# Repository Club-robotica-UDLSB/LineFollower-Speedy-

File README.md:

# LineFollower-Speedy-
Documentación del desarrollo del Seguidor de línea (El speedy)  

```plaintext
line_follower_project/
├── docs/                        # Documentación del proyecto
│   ├── README.md                # Descripción del proyecto
│   ├── schematics/              # Diagramas eléctricos y electrónicos
│   │   ├── circuit_diagram.png
│   │   └── PCB_design.pdf
│   └── requirements.md          # Lista de requisitos de hardware y software
├── hardware/                    # Archivos relacionados con el hardware
│   ├── BOM.csv                  # Lista de materiales (Bill of Materials)
│   ├── chassis_design/          # Diseños mecánicos (CAD)
│   │   ├── chassis.stl
│   │   └── chassis.fusion360
│   ├── sensors/                 # Información sobre sensores
│   │   └── sensor_datasheets/
│   │       └── IR_sensor.pdf
│   ├── motor_drivers/           # Archivos de controladores de motores
│   │   └── motor_driver_schematic.png
│   └── microcontroller/         # Configuración del microcontrolador
│       ├── pinout_diagram.png
│       └── firmware.hex
├── software/                    # Código fuente y programas
│   ├── main/                    # Código principal
│   │   ├── main.c
│   │   └── main.h
│   ├── libraries/               # Librerías reutilizables
│   │   ├── PID_controller.c
│   │   └── motor_control.c
│   ├── test/                    # Código para pruebas
│   │   ├── test_pid_controller.c
│   │   └── test_sensors.c
│   └── README.md                # Guía para compilar e instalar
├── tests/                       # Pruebas físicas y simulaciones
│   ├── simulations/             # Simulaciones virtuales
│   │   └── line_follower_simulation.py
│   ├── performance_logs/        # Registros de pruebas de rendimiento
│   │   ├── test_1_results.log
│   │   └── test_2_results.log
│   └── README.md                # Guía de pruebas
├── media/                       # Fotos, videos y otros recursos multimedia
│   ├── videos/
│   │   └── demo_video.mp4
│   └── images/
│       ├── prototype.jpg
│       └── testing.jpg
├── LICENSE                      # Licencia del proyecto
├── README.md                    # Introducción y explicación del proyecto
├── .gitignore                   # Archivos y carpetas a ignorar por Git
└── Makefile                     # Configuración para compilar el proyecto
```

## Descripción de las Carpetas y Archivos

### `docs/`
- **`README.md`**: Descripción general del proyecto.
- **`schematics/`**: Contiene diagramas eléctricos y diseños de PCB.
- **`requirements.md`**: Detalla los requisitos de hardware y software.

### `hardware/`
- **`BOM.csv`**: Lista de materiales necesarios para el proyecto.
- **`chassis_design/`**: Archivos de diseño mecánico del chasis.
- **`sensors/`**: Información técnica sobre los sensores utilizados.
- **`motor_drivers/`**: Esquemáticos de controladores de motores.
- **`microcontroller/`**: Configuración y firmware del microcontrolador.

### `software/`
- **`main/`**: Código principal del proyecto.
- **`libraries/`**: Librerías reutilizables (como controladores PID o control de motores).
- **`test/`**: Scripts para probar diferentes partes del sistema.

### `tests/`
- **`simulations/`**: Contiene simulaciones virtuales del robot.
- **`performance_logs/`**: Registros de pruebas realizadas en el hardware.

### `media/`
- **`videos/`**: Videos de demostración o pruebas del robot.
- **`images/`**: Fotos del prototipo, resultados de pruebas, etc.

### Archivos Raíz
- **`LICENSE`**: Licencia del proyecto.
- **`README.md`**: Introducción al proyecto.
- **`.gitignore`**: Archivos o carpetas que Git debe ignorar.
- **`Makefile`**: Instrucciones para compilar y ejecutar el proyecto.

---

## Notas Adicionales

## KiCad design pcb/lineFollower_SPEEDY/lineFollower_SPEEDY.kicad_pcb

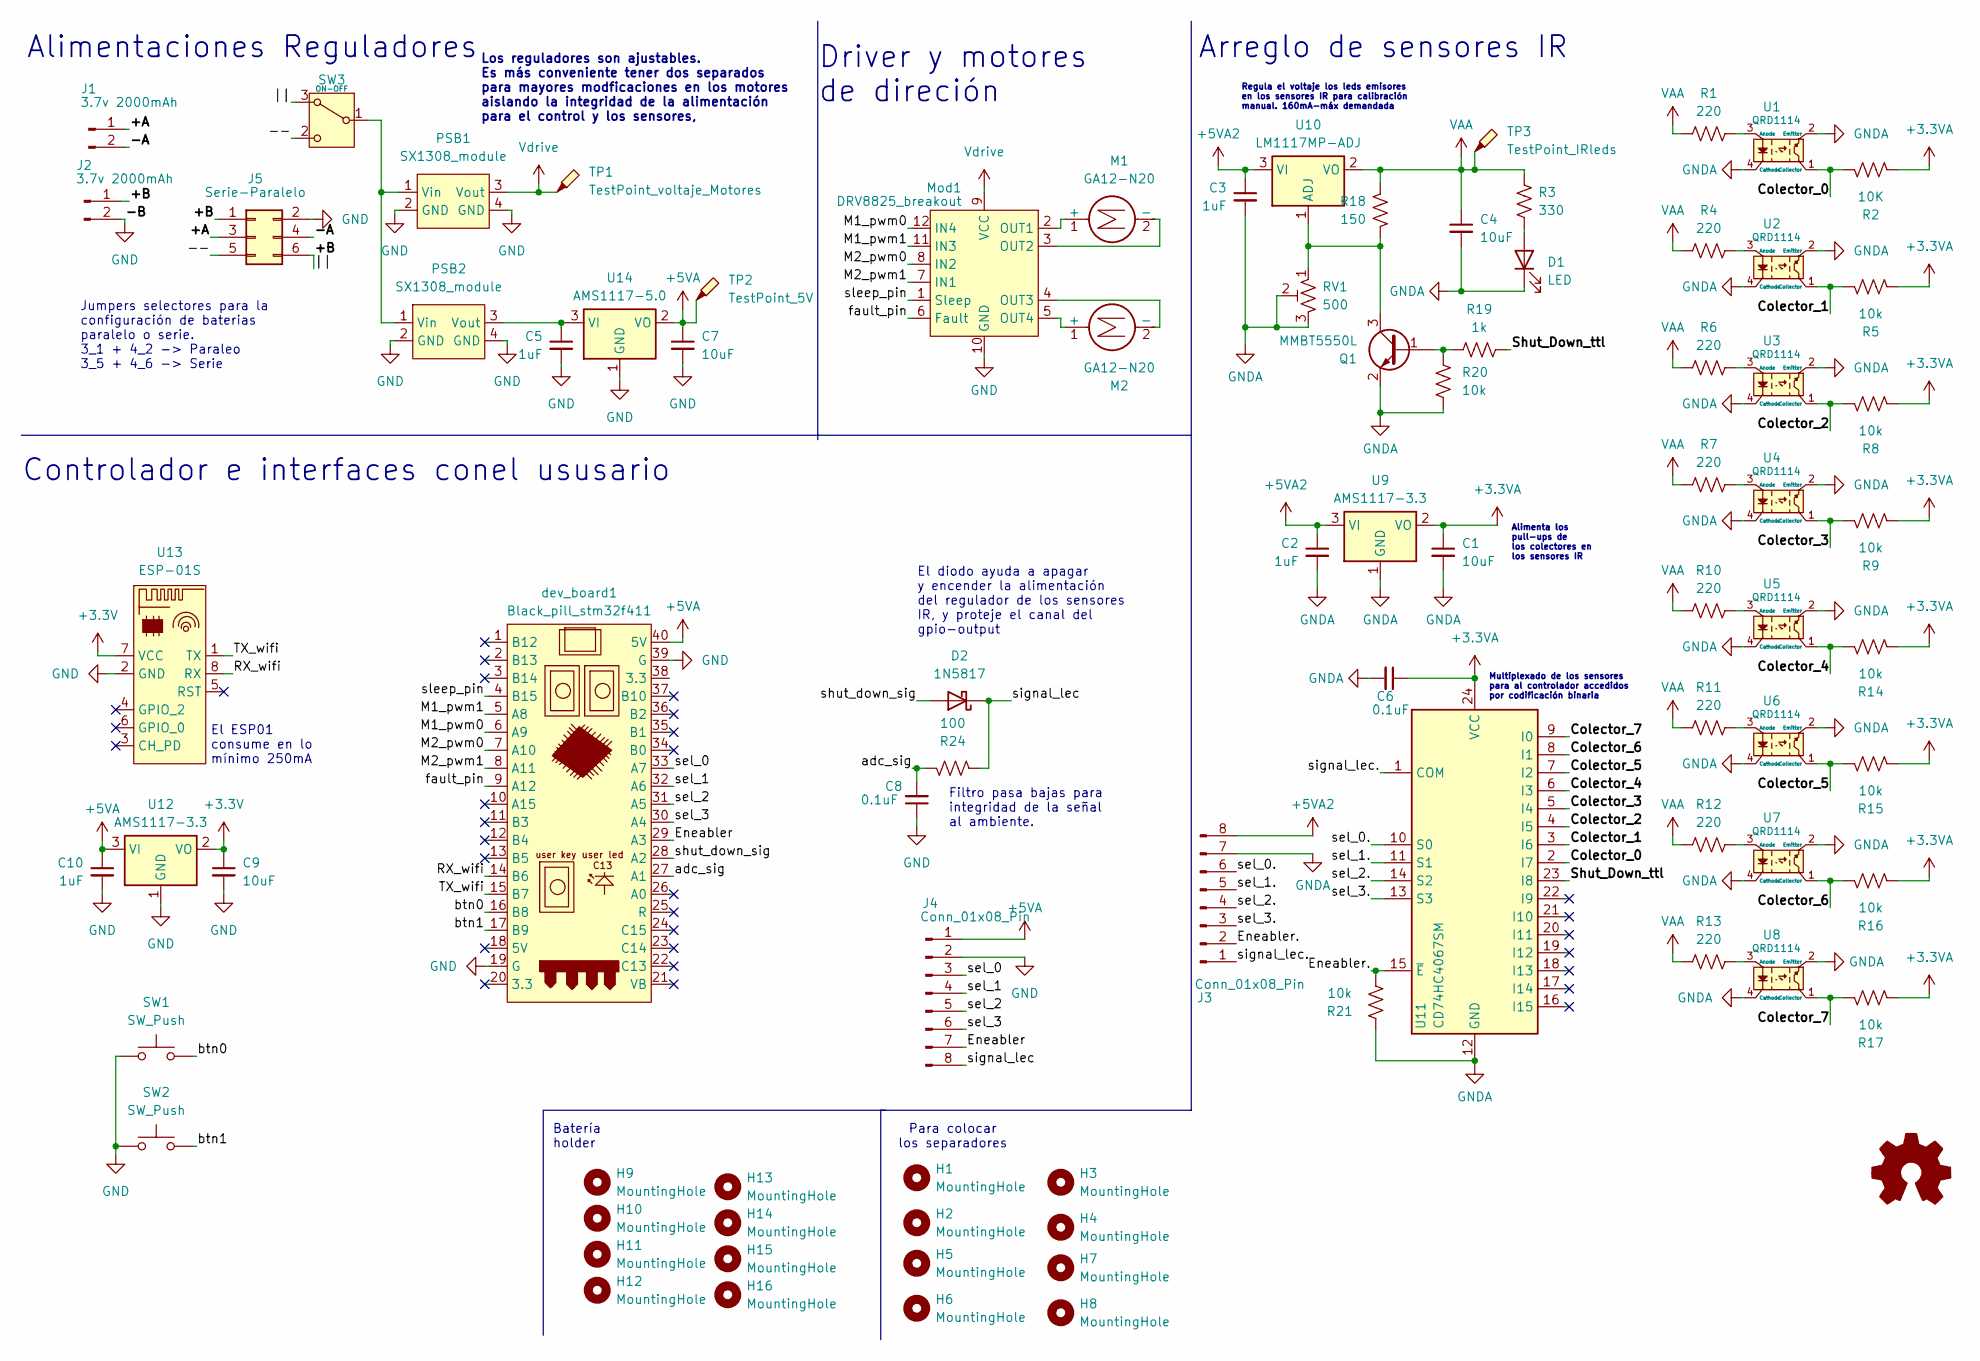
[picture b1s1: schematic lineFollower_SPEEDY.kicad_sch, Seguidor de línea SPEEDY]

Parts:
C1, C4, C7, C9: 10uF; C_0603_1608Metric_Pad1.08x0.95mm_HandSolder
C2, C3, C5, C10: 1uF; C_0603_1608Metric_Pad1.08x0.95mm_HandSolder
C6, C8: 0.1uF; C_0603_1608Metric_Pad1.08x0.95mm_HandSolder
D1: LED; LED_1206_3216Metric_Pad1.42x1.75mm_HandSolder
D2: 1N5817; D_DO-41_SOD81_P10.16mm_Horizontal
H1, H2, H3, H4, H5, H6, H7, H8, H9, H10, H11, H12, H13, H14, H15, H16: MountingHole; MountingHole_2.2mm_M2
J1, J2: 3.7v 2000mAh; JST_PH_S2B-PH-K_1x02_P2.00mm_Horizontal
J3, J4: Conn_01x08_Pin; PinHeader_1x08_P2.54mm_Horizontal
J5: Serie-Paralelo; PinHeader_2x03_P2.54mm_Vertical
M1, M2: GA12-N20; motor
Mod1: DRV8825_breakout; DRV8833_mod
PSB1, PSB2: SX1308_module; SX1308_mod
Q1: MMBT5550L; SOT-23
R1, R4, R6, R7, R10, R11, R12, R13: 220; R_0805_2012Metric_Pad1.20x1.40mm_HandSolder
R2: 10K; R_0805_2012Metric_Pad1.20x1.40mm_HandSolder
R3: 330; R_0805_2012Metric_Pad1.20x1.40mm_HandSolder
R5, R8, R9, R14, R15, R16, R17, R20, R21: 10k; R_0805_2012Metric_Pad1.20x1.40mm_HandSolder
R18: 150; R_0805_2012Metric_Pad1.20x1.40mm_HandSolder
R19: 1k; R_0805_2012Metric_Pad1.20x1.40mm_HandSolder
R24: 100; R_0805_2012Metric_Pad1.20x1.40mm_HandSolder
RV1: 500; Potentiometer_Bourns_3296W_Vertical
SW1, SW2: SW_Push; SW_Tactile_SPST_NO_Straight_CK_PTS636Sx25SMTRLFS
SW3: ON-OFF; SW_Slide-03_Wuerth-WS-SLTV_10x2.5x6.4_P2.54mm
TP1: TestPoint_voltaje_Motores; TestPoint_Loop_D2.54mm_Drill1.5mm_Beaded
TP2: TestPoint_5V; TestPoint_Loop_D2.54mm_Drill1.5mm_Beaded
TP3: TestPoint_IRleds; TestPoint_Loop_D2.54mm_Drill1.5mm_Beaded
U1, U2, U3, U4, U5, U6, U7, U8: QRD1114
U9, U12: AMS1117-3.3; SOT-223-3_TabPin2
U10: LM1117MP-ADJ; SOT-223-3_TabPin2
U11: CD74HC4067SM; SSOP-24_5.3x8.2mm_P0.65mm
U13: ESP-01S; ESP-01
U14: AMS1117-5.0; SOT-223-3_TabPin2
dev_board1: Black_pill_stm32f411; Electrosmith_Daisy_Seed

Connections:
+3.3V: C9.1, U12.2 (VO), U13.7 (VCC)
+3.3VA: C1.1, C6.1, R2.2, R5.2, R8.2, R9.2, R14.2, R15.2, R16.2, R17.2, U9.2 (VO), U11.24 (VCC)
+5VA: C7.1, C10.1, J4.1, TP2.1, U12.3 (VI), U14.2 (VO), dev_board1.40 (5V)
+5VA2: C2.1, C3.1, J3.8, U9.3 (VI), U10.3 (VI)
/+A: J1.1, J5.3
/+B: J2.1, J5.1, J5.6, SW3.3 (A)
/--: J5.5, SW3.2 (C)
/-A: J1.2, J5.4
/Colector_0: R2.1, U1.1 (Collector), U11.2 (I7)
/Colector_1: R5.1, U2.1 (Collector), U11.3 (I6)
/Colector_2: R8.1, U3.1 (Collector), U11.4 (I5)
/Colector_3: R9.1, U4.1 (Collector), U11.5 (I4)
/Colector_4: R14.1, U5.1 (Collector), U11.6 (I3)
/Colector_5: R15.1, U6.1 (Collector), U11.7 (I2)
/Colector_6: R16.1, U7.1 (Collector), U11.8 (I1)
/Colector_7: R17.1, U8.1 (Collector), U11.9 (I0)
/Eneabler: J4.7, dev_board1.29 (A3)
/Eneabler.: J3.2, R21.2, U11.15 (~E)
/M1_pwm0: Mod1.12 (IN4), dev_board1.6 (A9)
/M1_pwm1: Mod1.11 (IN3), dev_board1.5 (A8)
/M2_pwm0: Mod1.8 (IN2), dev_board1.7 (A10)
/M2_pwm1: Mod1.7 (IN1), dev_board1.8 (A11)
/RX_wifi: U13.8 (RX), dev_board1.14 (B6)
/Shut_Down_ttl: R19.1, U11.23 (I8)
/TX_wifi: U13.1 (TX), dev_board1.15 (B7)
/adc_sig: C8.2, R24.2, dev_board1.27 (A1)
/btn0: SW1.2, dev_board1.16 (B8)
/btn1: SW2.2, dev_board1.17 (B9)
/fault_pin: Mod1.6 (Fault), dev_board1.9 (A12)
/sel_0: J4.3, dev_board1.33 (A7)
/sel_0.: J3.6, U11.10 (S0)
/sel_1: J4.4, dev_board1.32 (A6)
/sel_1.: J3.5, U11.11 (S1)
/sel_2: J4.5, dev_board1.31 (A5)
/sel_2.: J3.4, U11.14 (S2)
/sel_3: J4.6, dev_board1.30 (A4)
/sel_3.: J3.3, U11.13 (S3)
/shut_down_sig: D2.2 (A), dev_board1.28 (A2)
/signal_lec: D2.1 (K), J4.8, R24.1
/signal_lec.: J3.1, U11.1 (COM)
/sleep_pin: Mod1.1 (Sleep), dev_board1.4 (B15)
GND: C5.2, C7.2, C8.1, C9.2, C10.2, J2.2, J4.2, J5.2, Mod1.10 (GND), PSB1.2 (GND), PSB1.4 (GND), PSB2.2 (GND), PSB2.4 (GND), SW1.1, SW2.1, U12.1 (GND), U13.2 (GND), U14.1 (GND), dev_board1.19 (G), dev_board1.39 (G)
GNDA: C1.2, C2.2, C3.2, C4.2, C6.2, D1.1 (K), J3.7, Q1.2 (E), R20.2, R21.1, RV1.2, RV1.3, U1.2 (Emitter), U1.4 (Cathode), U2.2 (Emitter), U2.4 (Cathode), U3.2 (Emitter), U3.4 (Cathode), U4.2 (Emitter), U4.4 (Cathode), U5.2 (Emitter), U5.4 (Cathode), U6.2 (Emitter), U6.4 (Cathode), U7.2 (Emitter), U7.4 (Cathode), U8.2 (Emitter), U8.4 (Cathode), U9.1 (GND), U11.12 (GND)
unnamed: D1.2 (A), R3.1
unnamed: M1.1 (+), Mod1.2 (OUT1)
unnamed: M1.2 (-), Mod1.3 (OUT2)
unnamed: M2.1 (+), Mod1.5 (OUT4)
unnamed: M2.2 (-), Mod1.4 (OUT3)
unnamed: PSB1.1 (Vin), PSB2.1 (Vin), SW3.1 (B)
unnamed: C5.1, PSB2.3 (Vout), U14.3 (VI)
unnamed: Q1.1 (B), R19.2, R20.1
unnamed: Q1.3 (C), R18.1, RV1.1, U10.1 (ADJ)
unnamed: R1.2, U1.3 (Anode)
unnamed: R4.2, U2.3 (Anode)
unnamed: R6.2, U3.3 (Anode)
unnamed: R7.2, U4.3 (Anode)
unnamed: R10.2, U5.3 (Anode)
unnamed: R11.2, U6.3 (Anode)
unnamed: R12.2, U7.3 (Anode)
unnamed: R13.2, U8.3 (Anode)
VAA: C4.1, R1.1, R3.2, R4.1, R6.1, R7.1, R10.1, R11.1, R12.1, R13.1, R18.2, TP3.1, U10.2 (VO)
Vdrive: Mod1.9 (VCC), PSB1.3 (Vout), TP1.1

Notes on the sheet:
Driver y motores de direción
Multiplexado de los sensores para al controlador accedidos por codificación binaria
El ESP01 consume en lo mínimo 250mA
El diodo ayuda a apagar y encender la alimentación del regulador de los sensores IR, y proteje el canal del gpio-output
Alimenta los pull-ups de los colectores en los sensores IR
Arreglo de sensores IR
Los reguladores son ajustables. Es más conveniente tener dos separados para mayores modficaciones en los motores aislando la integridad de la alimentación para el control y los sensores,
Regula el voltaje los leds emisores en los sensores IR para calibración manual. 160mA-máx demandada
Batería holder
Jumpers selectores para la configuración de baterias paralelo o serie. 3_1 + 4_2 -> Paraleo 3_5 + 4_6 -> Serie
Filtro pasa bajas para integridad de la señal al ambiente.
Alimentaciones Reguladores
Controlador e interfaces conel ususario
Para colocar los separadores

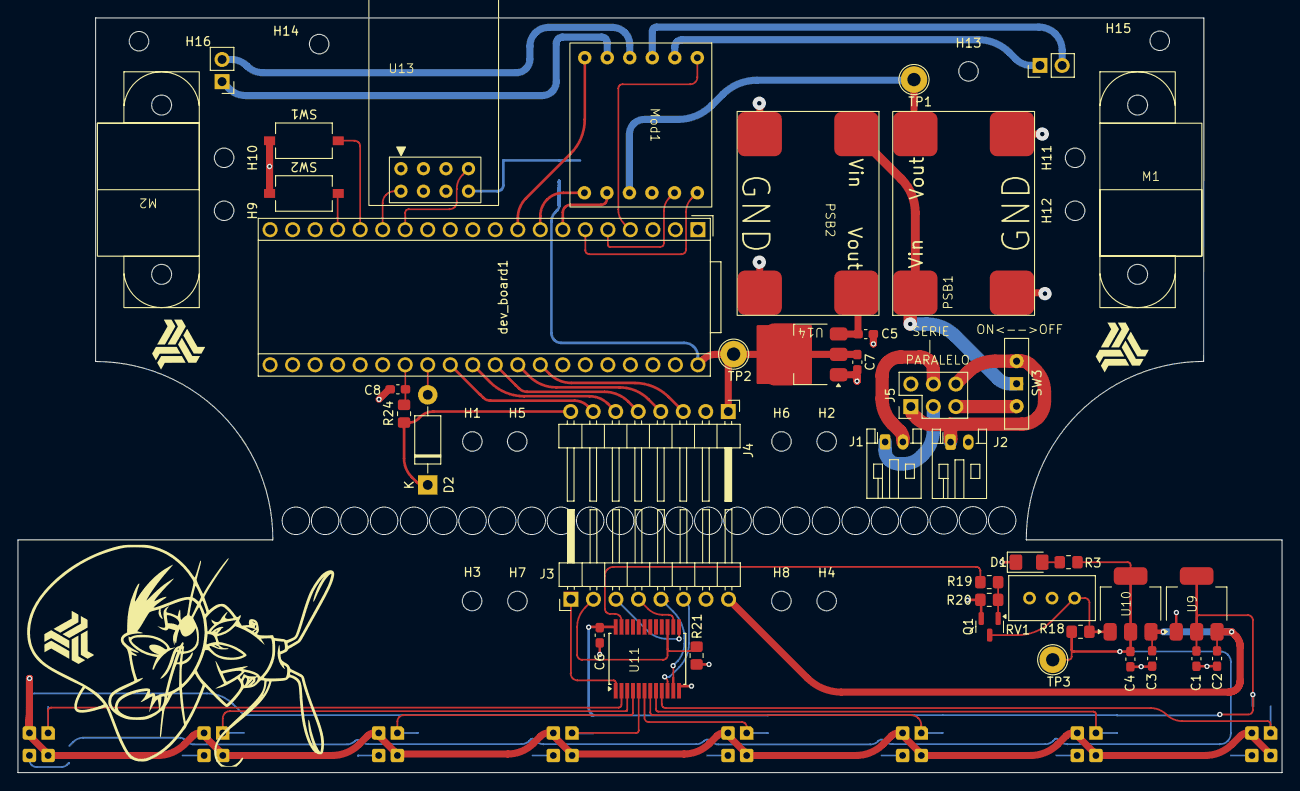
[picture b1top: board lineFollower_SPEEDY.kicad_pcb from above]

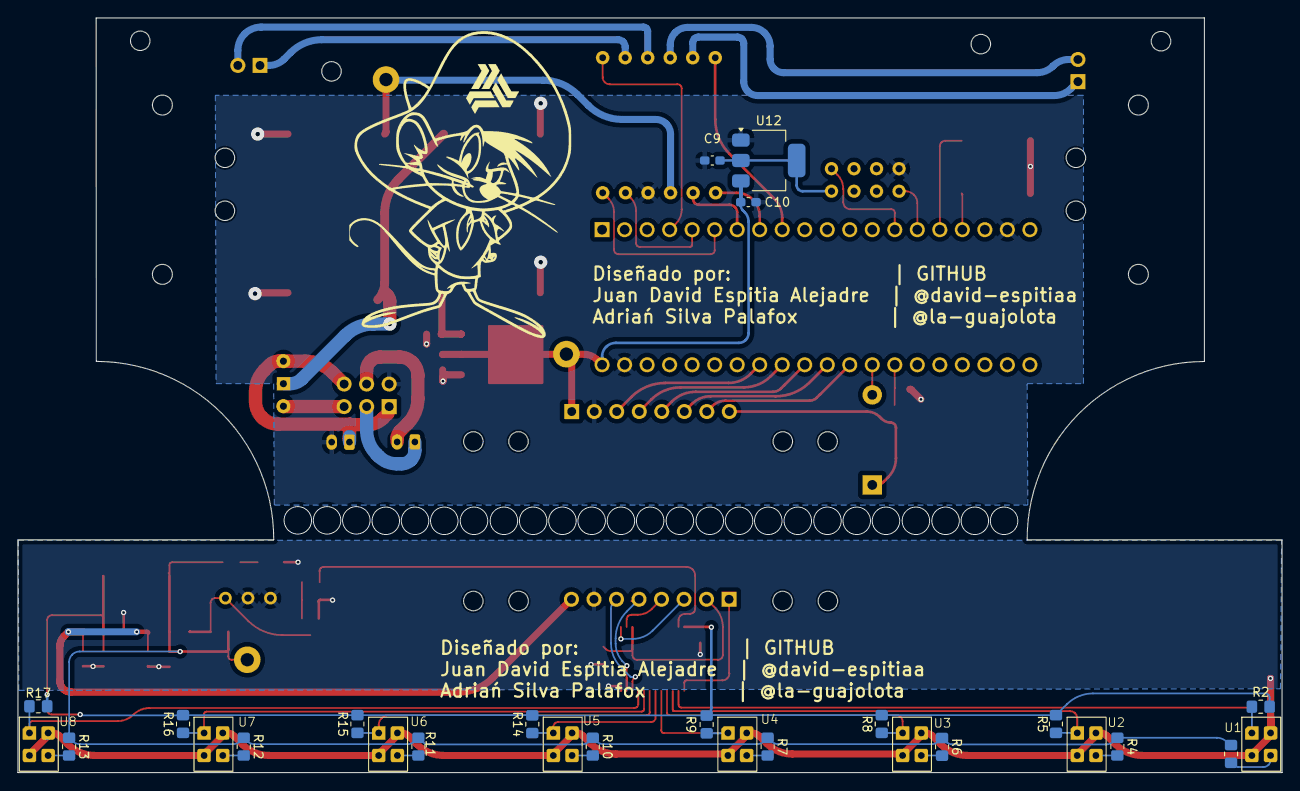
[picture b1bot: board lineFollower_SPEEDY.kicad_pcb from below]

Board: 2 copper layers, 142.6 x 85.1 mm, 83 parts (27 on the bottom side), 62 nets.

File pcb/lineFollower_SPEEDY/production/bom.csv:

Designator,Footprint,Quantity,Value,LCSC Part #
"C1, C4, C7, C9",0603,4,10uF,
"C10, C2, C3, C5",0603,4,1uF,
"C6, C8",0603,2,0.1uF,
D1,1206,1,LED,
D2,D_DO-41_SOD81_P10.16mm_Horizontal,1,1N5817,
DEV_BOARD1,Electrosmith_Daisy_Seed,1,Black_pill_stm32f411,
"J1, J2",JST_PH_S2B-PH-K_1x02_P2.00mm_Horizontal,2,3.7v 2000mAh,
"J3, J4",PinHeader_1x08_P2.54mm_Horizontal,2,Conn_01x08_Pin,
J5,PinHeader_2x03_P2.54mm_Vertical,1,Serie-Paralelo,
"M1, M2",motor,2,GA12-N20,
MOD1,DRV8833_mod,1,DRV8825_breakout,
"PSB1, PSB2",SX1308_mod,2,SX1308_module,
Q1,SOT-23,1,MMBT5550L,
"R1, R10, R11, R12, R13, R4, R6, R7",0805,8,220,
"R14, R15, R16, R17, R2, R20, R21, R5, R8, R9",0805,10,10k,
R18,0805,1,150,
R19,0805,1,1k,
R24,0805,1,100,
R3,0805,1,330,
RV1,Potentiometer_Bourns_3296W_Vertical,1,500,
"SW1, SW2",SW_Tactile_SPST_NO_Straight_CK_PTS636Sx25SMTRLFS,2,SW_Push,
SW3,SW_Slide-03_Wuerth-WS-SLTV_10x2.5x6.4_P2.54mm,1,ON-OFF,
TP1,TestPoint_Loop_D2.54mm_Drill1.5mm_Beaded,1,TestPoint_voltaje_Motores,
TP2,TestPoint_Loop_D2.54mm_Drill1.5mm_Beaded,1,TestPoint_5V,
TP3,TestPoint_Loop_D2.54mm_Drill1.5mm_Beaded,1,TestPoint_IRleds,
"U1, U2, U3, U4, U5, U6, U7, U8",QRD1114,8,QRD1114,
U10,SOT-223-3_TabPin2,1,LM1117MP-ADJ,
U11,SSOP-24_5.3x8.2mm_P0.65mm,1,CD74HC4067SM,
"U12, U9",SOT-223-3_TabPin2,2,AMS1117-3.3,
U13,ESP-01,1,ESP-01S,
U14,SOT-223-3_TabPin2,1,AMS1117-5.0,

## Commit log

2025-05-01 primer commit
2025-05-01 primer commit firmware
